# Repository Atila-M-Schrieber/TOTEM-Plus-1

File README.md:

<picture align="center">
  <source media="(prefers-color-scheme: dark)" srcset="/docs/images/TOTEM_logo_dark.svg">
  <source media="(prefers-color-scheme: light)" srcset="/docs/images/TOTEM_logo_bright.svg">
  
</picture>

<h1 align="center">T O T E M</h1>
<h2 align="center">Plus 1</h2>

TOTEM Plus 1 is a modified version of the TOTEM keyboard, with an extra pinky key.
It is a 40 key column-staggered choc split keyboard. It is meant to be used with a SEEED XIAO BLE or RP2040.
The build process is pretty much identical, except you need electronics for two more keys.
(Sockets, diodes, switches, and keycaps)
[Here](https://www.hackster.io/geist/totem-a-tiny-splitkeyboard-with-splay-cb2e43) you can read about the process of making it.

The case can fit into a magnetic travel case, like the one
made by [Compression Keyboards](https://compressionkeyboards.com/products/4c-3d-printed-case-kit).
The current V2 case is still missing accenting and some optimization, but is otherwise ready for use,
and works great with the V0 travel case.

While the layout is pretty much identical to the [KLOR KONRAD](https://github.com/GEIGEIGEIST/KLOR),
I prefer the æsthetics of the TOTEM, and I have no need for a rotary encoder on this keyboard.
Also, I wanted to dip my toes into PCB editing, and this seemed like a slightly bigger challenge
(it was) than removing the rotary encoder from the KLOR.

### Additional features:
- [x] I like the idea of using a switch (like the on/off one) as a way to turn a layer on/off,
      especially for a usecase like gaming. Since I'm going to use this wirelessly, I might add
      another switch (same as the power on/off switch) on top of where where the TRRS
      jack would go. I can probably add the footprint without even removing the TRRS footprints.
      This would mean another row or column from one of the UART pins
        - If I'm using the UART pins for something else, like trackpoint support, this won't work
          (or only on one side of the keyboard, ie 'gaming mode' switch on left side, trackpoint on right)
        - In implementing this **I swapped the poles of the TRRS jack** (GND -> TX -> VCC -> GND), so take note
          if you do end up using the wired version and need to debug the TTRS cable (for some reason).
        - There is a lot of overlap with the TRRS through holes - while it might be harder to solder
          due to the conduction, there is plenty of space to solder the switch leads.
    - Alternatively I can add an I/O expander (MCP23017), which is already supported in ZMK
- [x] Splitting the current top half of the case into top and middle sections, where the middle section
      would be the key grid + the 'skirt' of the thumb cluster. This would eliminate the need for supports,
      and would make the exposed key grid take on the texture of the print bed.
      It also allows the removal of the top & bottom parts without having to remove all the keycaps.
- [ ] The current tenting and anti-slip solutions work, but could be improved,
      for example by integrating magnetic stands, for example using a MagSafe phone stand as the mounting and tenting solution.
- [ ] Trackpoint support: ([see this pull request / fork](https://github.com/zmkfirmware/zmk/pull/1751))
      This would be a replacement for the TRRS jacks, since it uses UART.
      I have ordered [this module](https://www.aliexpress.com/item/1005004696754100.html),
      so I'll see if/how I can use it.
***

(The Plus in the 'totem pole' logo is (supposed to be) a hammerhead)

## LAYOUT

***

## PCB

[Here](/PCB/) you can find the KiCad files and Gerbers for the TOTEM.

***

## CASE

You can use the TOTEM without a case, but [here](/case/) you can find one I made for it.

***

## BUILD GUIDE

The build guide for the TOTEM can be found [here](/docs/buildguide.md).

***

## FIRMWARE

[My ZMK config](https://github.com/Atila-M-Schrieber/zmk-config) for the TOTEM Plus 1 (wireless with a dongle, using the XIAO BLE)

[Original dongle ZMK config](https://github.com/eigatech/zmk-config/tree/totem-dongle) for the TOTEM wireless + dongle build

***

## PHOTOS

This is the TOTEM Plus 1 in the V2 case optimized for FDM printing.
The case was printed using Gembird gray PETG on an Ender 3 V3 Plus with a 0.6mm nozzle and 0.3mm layer height.
The keycaps used can be found [here](https://github.com/sporkus/PseudoMakeMeKeyCapProfiles) (the Chicago Stenographer version),
and were printed on a Prusa SL1.

The magnet arrangement for the travel case:

The travel case:

The current V0 travel case is not yet properly optimized for FDM printing,
and is missing some features, like having storage for the dongle.

***

## CREDITS

These credits are by GEIST.

### INSPIRATION

I've added the additional pinky key to make the TOTEM compatible with the layout boards like the [Balbuzard](https://github.com/brow/balbuzard) by [Tom Brow](https://github.com/brow) and the [Osprette](https://github.com/smores56/osprette) by [Sam Mohr](https://github.com/smores56) use, where you put the keybinding of the top left and right keys on an outer pinky key.

### HELP FIXING THINGS

People who helped me create this board and fix stuff

#### PCB
- [Marco "Bob"](https://github.com/GroooveBob)

#### CASE
- [Freya](https://github.com/freya-irl)
- [Bubbleology](https://github.com/bubbleology)

#### FIRMWARE
- [Cem Aksoylar](https://github.com/caksoylar)
- [Grinnie](https://github.com/regicidalplutophage)
- [Alaa Saad Mansour](https://github.com/AlaaSaadAbdo)
- [pekudzu](https://github.com/pekudzu)

If you build a TOTEM I would be pretty happy to see some pictures. And if you want to leave me a tip you can do this [here](https://ko-fi.com/geigeigeist) (but please don't feel pressured)

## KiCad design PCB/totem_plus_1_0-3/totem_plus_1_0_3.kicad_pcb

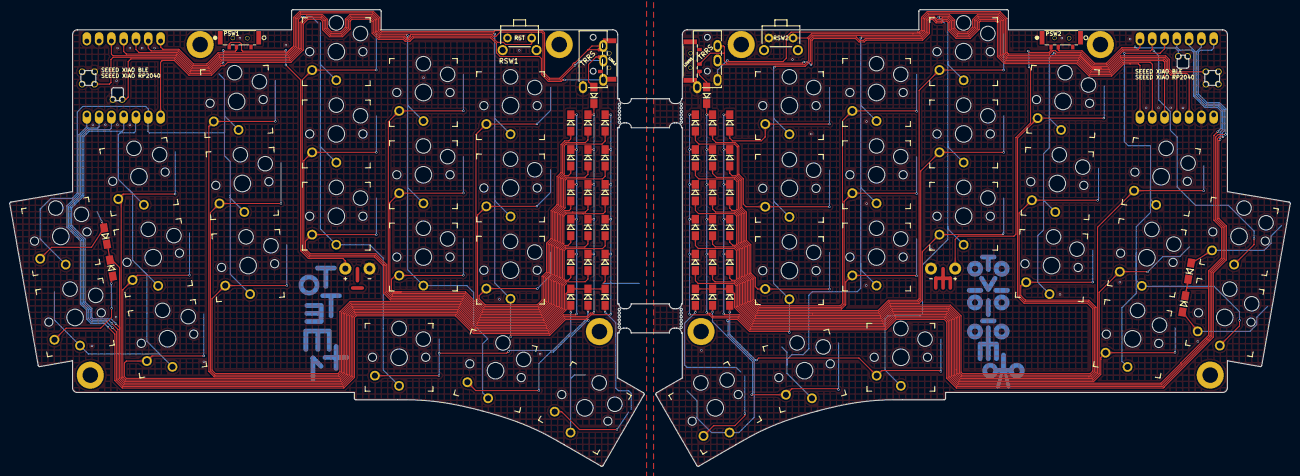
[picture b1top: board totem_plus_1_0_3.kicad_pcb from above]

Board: 2 copper layers, 264.6 x 94.4 mm, 96 parts (0 on the bottom side), 74 nets.

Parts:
BAT+1, BAT+2: +; BatteryPad
BATGND1, BATGND2: -; BatteryPad
DL1, DL2, DL3, DL4, DL5, DL6, DL7, DL8, DL9, DL10, DL11, DL12, DL13, DL14, DL15, DL16, DL17, DL18, DL19, DL20: D_Small; Diode_SOD123
DLL1: D_Small; Diode_SOD123
DR1, DR2, DR3, DR4, DR5, DR6, DR7, DR8, DR9, DR10, DR11, DR12, DR13, DR14, DR15, DR16, DR17, DR18, DR19, DR20: D_Small; Diode_SOD123
DRL1: D_Small; Diode_SOD123
J1, J2: MJ-4PP-9; MJ-4PP-9_1side
LSWL1: SW_SPDT; MSK12C02
LSWR1: SW_SPDT; MSK12C02
PSW1, PSW2: SW_SPDT; MSK12C02
RSW1, RSW2: SW_Push; SKHLLCA010
SWL1, SWL2, SWL3, SWL4, SWL5, SWL6, SWL7, SWL8, SWL9, SWL10, SWL11, SWL12, SWL13, SWL14, SWL15, SWL16, SWL17, SWL18, SWL19, SWL20: SW_Push_45deg; Kailh_socket_PG1350_optional
SWR1, SWR2, SWR3, SWR4, SWR5, SWR6, SWR7, SWR8, SWR9, SWR10, SWR11, SWR12, SWR13, SWR14, SWR15, SWR16, SWR17, SWR18, SWR19, SWR20: SW_Push_45deg; Kailh_socket_PG1350_optional
U1, U2: xiao-ble; xiao-ble-smd-cutout

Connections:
BAT+_L: PSW1.2 (B), U1.19 (BAT)
BAT+_R: PSW2.2 (B), U2.19 (BAT)
COL0_L: SWL1.1, SWL6.1, SWL11.1, SWL16.1, U1.5 (A8_SDA/0.04_H)
COL0_R: SWR1.1, SWR6.1, SWR11.1, SWR16.1, U2.5 (A8_SDA/0.04_H)
COL1_L: SWL2.1, SWL7.1, SWL12.1, SWL17.1, U1.6 (A9_SCL/0.05_H)
COL1_R: SWR2.1, SWR7.1, SWR12.1, SWR17.1, U2.6 (A9_SCL/0.05_H)
COL2_L: SWL3.1, SWL8.1, SWL13.1, SWL18.1, U1.11 (A6_MOSI/1.15)
COL2_R: SWR3.1, SWR8.1, SWR13.1, SWR18.1, U2.11 (A6_MOSI/1.15)
COL3_L: SWL4.1, SWL9.1, SWL14.1, SWL19.1, U1.10 (A5_MISO/1.14)
COL3_R: SWR4.1, SWR9.1, SWR14.1, SWR19.1, U2.10 (A5_MISO/1.14)
COL4_L: SWL5.1, SWL10.1, SWL15.1, SWL20.1, U1.9 (A7_SCK/1.13)
COL4_R: SWR5.1, SWR10.1, SWR15.1, SWR20.1, U2.9 (A7_SCK/1.13)
COL5_L: J1.B, LSWL1.3 (C), U1.8 (B9_RX/1.12)
COL5_R: J2.B, LSWR1.2 (B), U2.8 (B9_RX/1.12)
GND_L: BATGND1.1, J1.A, RSW1.2, U1.13 (GND), U1.18 (GND), U1.20 (GND)
GND_R: BATGND2.1, J2.A, RSW2.2, U2.13 (GND), U2.18 (GND), U2.20 (GND)
unnamed: DL1.2 (A), SWL1.2
unnamed: DL2.2 (A), SWL2.2
unnamed: DL3.2 (A), SWL3.2
unnamed: DL4.2 (A), SWL4.2
unnamed: DL5.2 (A), SWL5.2
unnamed: DL6.2 (A), SWL6.2
unnamed: DL7.2 (A), SWL7.2
unnamed: DL8.2 (A), SWL8.2
unnamed: DL9.2 (A), SWL9.2
unnamed: DL10.2 (A), SWL10.2
unnamed: DL11.2 (A), SWL11.2
unnamed: DL12.2 (A), SWL12.2
unnamed: DL13.2 (A), SWL13.2
unnamed: DL14.2 (A), SWL14.2
unnamed: DL15.2 (A), SWL15.2
unnamed: DL16.2 (A), SWL16.2
unnamed: DL17.2 (A), SWL17.2
unnamed: DL18.2 (A), SWL18.2
unnamed: DL19.2 (A), SWL19.2
unnamed: DL20.2 (A), SWL20.2
unnamed: DLL1.2 (A), LSWL1.2 (B)
unnamed: DR1.2 (A), SWR1.2
unnamed: DR2.2 (A), SWR2.2
unnamed: DR3.2 (A), SWR3.2
unnamed: DR4.2 (A), SWR4.2
unnamed: DR5.2 (A), SWR5.2
unnamed: DR6.2 (A), SWR6.2
unnamed: DR7.2 (A), SWR7.2
unnamed: DR8.2 (A), SWR8.2
unnamed: DR9.2 (A), SWR9.2
unnamed: DR10.2 (A), SWR10.2
unnamed: DR11.2 (A), SWR11.2
unnamed: DR12.2 (A), SWR12.2
unnamed: DR13.2 (A), SWR13.2
unnamed: DR14.2 (A), SWR14.2
unnamed: DR15.2 (A), SWR15.2
unnamed: DR16.2 (A), SWR16.2
unnamed: DR20.2 (A), SWR17.2
unnamed: DR17.2 (A), SWR18.2
unnamed: DR18.2 (A), SWR19.2
unnamed: DR19.2 (A), SWR20.2
unnamed: DRL1.2 (A), LSWR1.3 (C)
RESET_L: RSW1.1, U1.17 (RESET)
RESET_R: RSW2.1, U2.17 (RESET)
ROW0_L: DL1.1 (K), DL2.1 (K), DL3.1 (K), DL4.1 (K), DL5.1 (K), U1.1 (A2/0.02_H)
ROW0_R: DR1.1 (K), DR2.1 (K), DR3.1 (K), DR4.1 (K), DR5.1 (K), U2.1 (A2/0.02_H)
ROW1_L: DL6.1 (K), DL7.1 (K), DL8.1 (K), DL9.1 (K), DL10.1 (K), DLL1.1 (K), U1.2 (A4/0.03_H)
ROW1_R: DR6.1 (K), DR7.1 (K), DR8.1 (K), DR9.1 (K), DR10.1 (K), DRL1.1 (K), U2.2 (A4/0.03_H)
ROW2_L: DL11.1 (K), DL12.1 (K), DL13.1 (K), DL14.1 (K), DL15.1 (K), U1.3 (A10/0.28)
ROW2_R: DR11.1 (K), DR12.1 (K), DR13.1 (K), DR14.1 (K), DR15.1 (K), U2.3 (A10/0.28)
ROW3_L: DL16.1 (K), DL17.1 (K), DL18.1 (K), DL19.1 (K), DL20.1 (K), U1.4 (A11/0.29)
ROW3_R: DR16.1 (K), DR17.1 (K), DR18.1 (K), DR19.1 (K), DR20.1 (K), U2.4 (A11/0.29)
TX_L: J1.D, U1.7 (B8_TX/1.11)
TX_R: J2.D, U2.7 (B8_TX/1.11)
VBAT_L: BAT+1.1, PSW1.3 (C)
VBAT_R: BAT+2.1, PSW2.3 (C)
VCC_L: J1.C, U1.12 (3V3)
VCC_R: J2.C, U2.12 (3V3)

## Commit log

2024-07-09 Initial update from original
2024-07-10 Updated schematic to match design. Placed both new switches in the correct position. Re-routed traces on left side. Next: rerouting on the right side.
2024-07-10 Renamed the PCB directory to match the new keyboard name
2024-07-10 Fixed key designations on right side, and cleared right-edge tracks.
2024-07-11 Re-routed everything successfully.
2024-07-12 Re-did a bit on the right end, mostly for aesthetics. Fixed discontinuity in PCB edge cut. Routing should (hopefully) be final.
2024-07-13 Small PCB adjustments, README update
2024-07-13 Added option to add a switch (like the power switch) instead of a TRRS jack as a 'key' - ie as a layer switch
2024-07-13 Added silkscreen art, and small readme changes
2024-07-13 Modified logo
2024-07-13 Additional silkscreen art
2024-07-13 Silkscreen changes so things are more visible around the now-cluttered TRRS jacks
2024-07-14 Added teardrops to vias, exported gerbers (the .zip should now work)
2024-07-15 Fixed gerber zip
2024-08-11 updates README with progress and firmware link
2024-08-15 updates PCB to remove the self-grounding error, and updates the README accordingly
2025-01-06 Added case, updated README
2025-01-06 Fixed README
2025-01-10 Updated case design to V2, updated README
2025-01-10 Fix to STL
2025-01-19 Adds travel case, and updates build guide.
2025-01-19 file name fix
